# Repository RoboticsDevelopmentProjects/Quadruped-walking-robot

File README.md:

###千葉工業大学　中嶋研究室　学科プロジェクト
####ロボティクスプロジェクト1～4で作成したソースコードおよびCADデータを一括管理するためのレポジトリ

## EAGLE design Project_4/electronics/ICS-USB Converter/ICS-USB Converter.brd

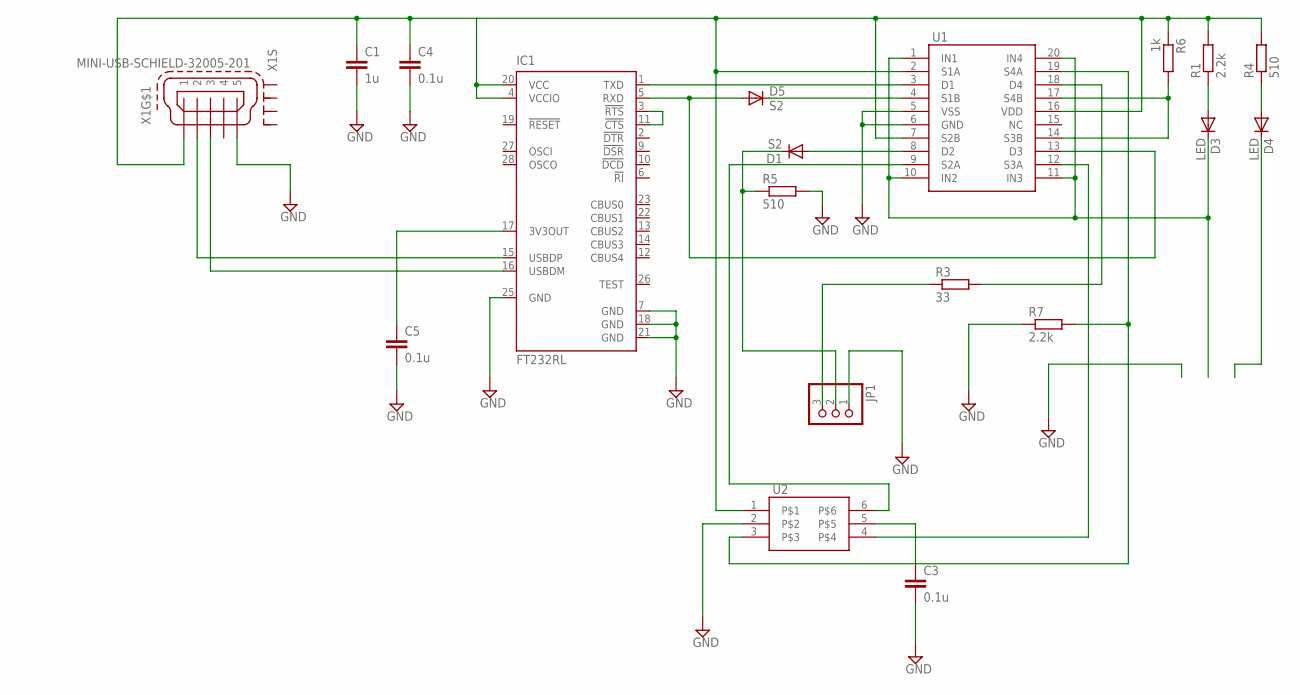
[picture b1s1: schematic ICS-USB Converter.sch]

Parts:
C1: 1u; C2012
C3, C4, C5: 0.1u; C1608
D1, D5: S2; SOD523
D3, D4: LED; SOD523
IC1: FT232RL; SSOP28
JP1: PINHD-1X3; 1X03
R1, R7: 2.2k; C1608
R3: 33; C1608
R4, R5: 510; C1608
R6: 1k; C1608
U1: ADG734; TSSOP20
U2: HA5SOT23-6; SOT23-6
X1: MINI-USB-SCHIELD-32005-201; 32005-201

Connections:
GND: C1.2, C3.2, C4.2, C5.2, IC1.7 (GND), IC1.18 (GND), IC1.21 (GND), IC1.25 (GND), JP1.1, R5.2, R7.1, U1.5 (VSS), U1.6 (GND), U2.2, X1.5
unnamed: IC1.3 (!RTS), IC1.11 (!CTS)
unnamed: IC1.1 (TXD), U1.3 (D1)
unnamed: U1.12 (S3A), U2.4
unnamed: D5.A, IC1.5 (RXD), U1.13 (D3)
unnamed: D5.C, U1.4 (S1B)
unnamed: R7.2, U1.19 (S4A), U2.3
unnamed: C5.1, IC1.17 (3V3OUT)
unnamed: D1.A, U1.8 (D2)
unnamed: D1.C, JP1.2, R5.1
unnamed: JP1.3, R3.1
unnamed: R6.2, U1.14 (S3B), U1.17 (S4B)
unnamed: D3.A, R1.1
unnamed: D4.A, R4.1
unnamed: IC1.15 (USBDP), X1.2
unnamed: IC1.16 (USBDM), X1.3
unnamed: R3.2, U1.18 (D4)
unnamed: D3.C, U1.1 (IN1), U1.10 (IN2), U1.11 (IN3), U1.20 (IN4)
unnamed: C1.1, C4.1, IC1.4 (VCCIO), IC1.20 (VCC), R1.2, R4.2, R6.1, U1.2 (S1A), U1.7 (S2B), U1.16 (VDD), U2.1, X1.1
unnamed: U1.9 (S2A), U2.6
unnamed: C3.1, U2.5

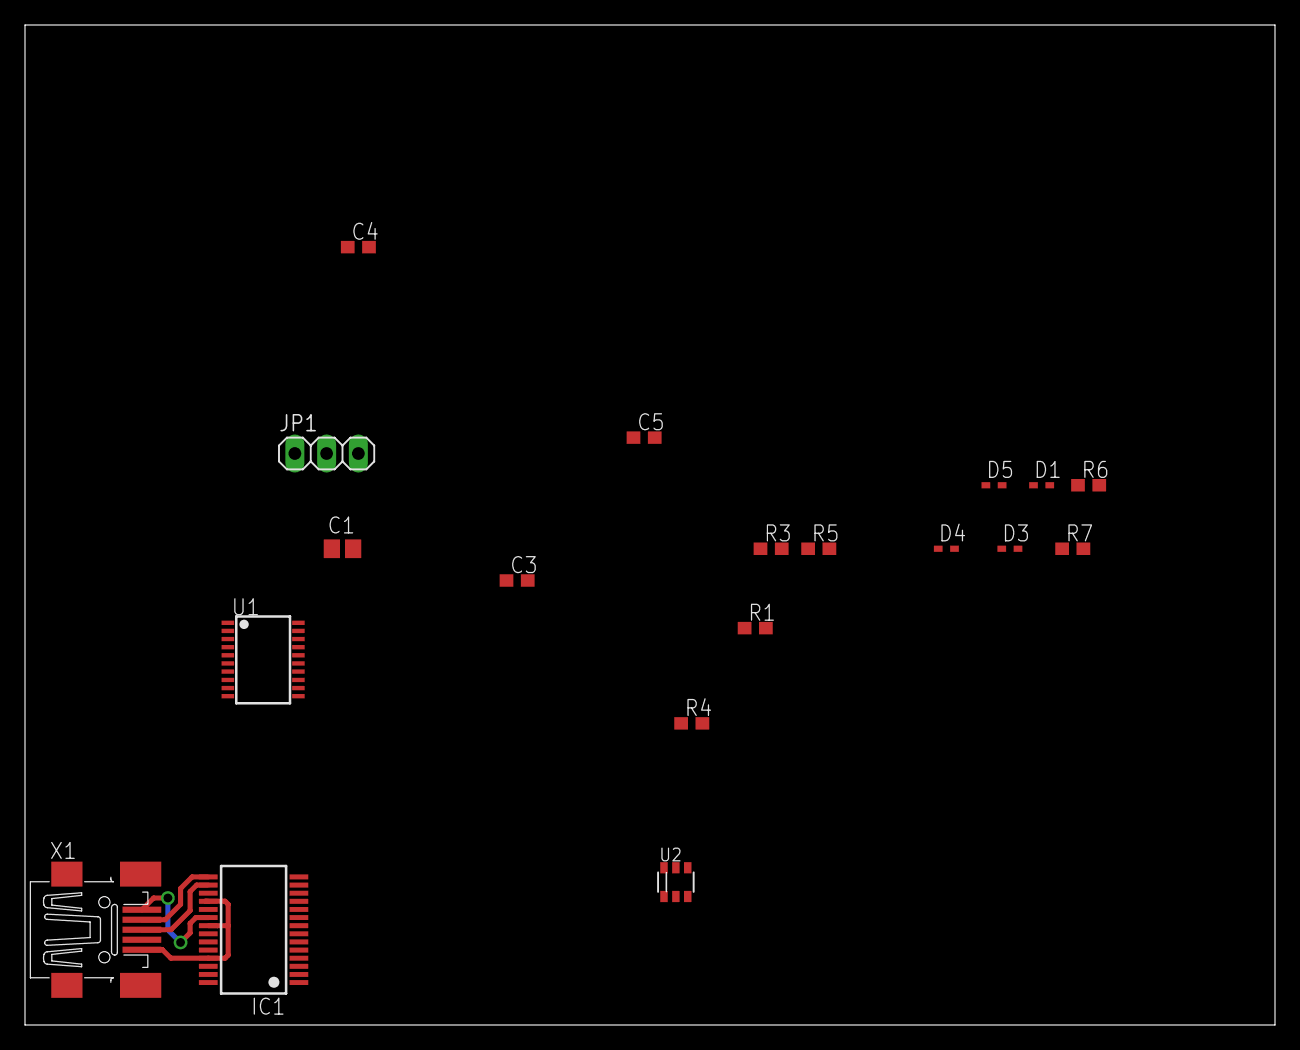
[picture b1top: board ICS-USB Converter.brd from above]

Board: 2 copper layers, 100.0 x 80.0 mm, 19 parts (0 on the bottom side), 21 nets.

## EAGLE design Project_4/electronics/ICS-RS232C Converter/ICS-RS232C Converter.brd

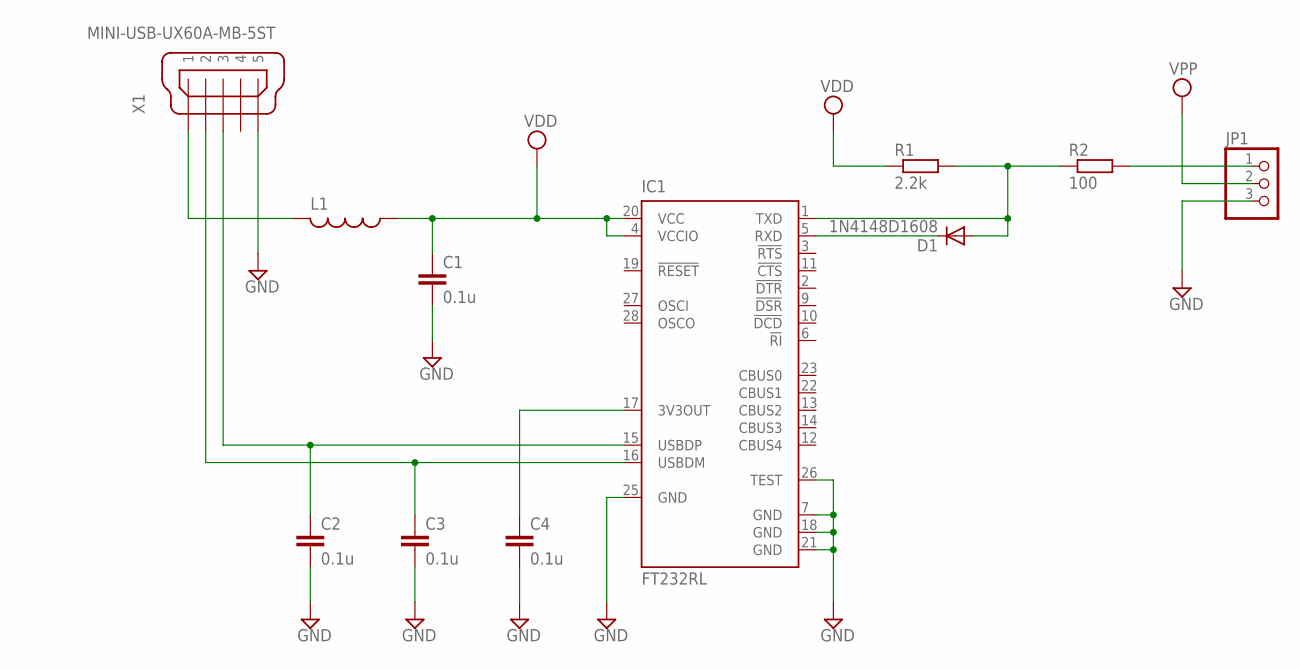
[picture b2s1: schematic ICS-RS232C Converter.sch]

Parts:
C1, C2, C3, C4: 0.1u; C1608
D1: 1N4148D1608; D1608
IC1: FT232RL; SSOP28
JP1: PINHD-1X3; 1X03
L1: L-USL2012C; L2012C
R1: 2.2k; C1608
R2: 100; C1608
X1: MINI-USB-UX60A-MB-5ST; UX60A-MB-5ST

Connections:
GND: C1.2, C2.2, C3.2, C4.2, IC1.7 (GND), IC1.18 (GND), IC1.21 (GND), IC1.25 (GND), IC1.26 (TEST), JP1.3, X1.5
unnamed: L1.2, X1.1
unnamed: C3.1, IC1.16 (USBDM), X1.2
unnamed: C2.1, IC1.15 (USBDP), X1.3
unnamed: C4.1, IC1.17 (3V3OUT)
unnamed: D1.2 (C), IC1.5 (RXD)
unnamed: D1.1 (A), IC1.1 (TXD), R1.2, R2.1
unnamed: JP1.1, R2.2
VDD: C1.1, IC1.4 (VCCIO), IC1.20 (VCC), L1.1, R1.1
VPP: JP1.2

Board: 2 copper layers, 11 parts (0 on the bottom side), 9 nets, no tracks yet.

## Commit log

2014-04-03 レポジトリを分割しました
2014-04-04 Update design file
2014-04-04 stl upload
2014-04-11 add electronics folder
2014-05-13 update mechanic file
2014-05-15 make choreonoid_model and set simulater
2014-05-20 Update SerialServo Program
2014-05-21 サーボの速度を可変できるよう変更
2014-05-21 角度が読めないバグを修正
2014-05-27 change COM Port
2014-06-11 Upload ImageProcessing source
2014-06-11 update mecahnic file
2014-07-31 不要なファイルを削除
